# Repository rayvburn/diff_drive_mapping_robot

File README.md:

# diff_drive_mapping_robot
This is the ROS driver for the Raspberry Pi based differential drive robot that was built as a part of my MSc thesis. 

Base of the robot was made of acrylic glass. The locomotion is provided by 3 wheels, including 1 caster. The two-wheel differential drive based on DC motors makes the machine nonholonomic.

Within the electronic part of the robot's construction, a printed circuit board was designed. All the necessary electronical components including reflective sensors used to measure the distance from obstacles were placed on the board. The sensor providing the largest amount of data is the camera. It is integrated with the Raspberry Pi microcomputer. The extension of the microcomputer's tasks to the reading of wheel positions and motor control allowed to use its resources efficiently and to avoid adding an extra microcontroller.

Looking at the PCB project (made in KiCad) should give you some idea what components to use if you plan to make a copy of it.

The robot is intended to work together with remote machine like PC that performs some more sophisticated duties. It was created to interface with ORB-SLAM2 well.

# Installation instructions

The package contents should be placed and compiled both on PC and on RPi's SD card. It was tested only on ROS Kinetic (running on Ubuntu 16.04).

wiringPi library is needed (http://wiringpi.com/). A script to install it on Raspberry Pi was provided.

raspicam_node (https://github.com/UbiquityRobotics/raspicam_node) is required if you will use Raspberry Pi camera but isn't marked as dependency for the package. If you don't plan to use it, just remove appropriate line in robot/robot_offline .launch file (the one with inclusion of raspicam_node's .launch).

# Usage

If a Raspberry Pi is present within a local Wi-Fi network

    roslaunch diff_drive_mapping_robot robot.launch

or for testing purposes (no RPi)

    roslaunch diff_drive_mapping_robot robot_offline.launch
    
# Notes
I highly recommend acquiring an Ubuntu image adequate for Raspberry Pi (with ROS Kinetic already installed) from here: https://downloads.ubiquityrobotics.com/pi.html

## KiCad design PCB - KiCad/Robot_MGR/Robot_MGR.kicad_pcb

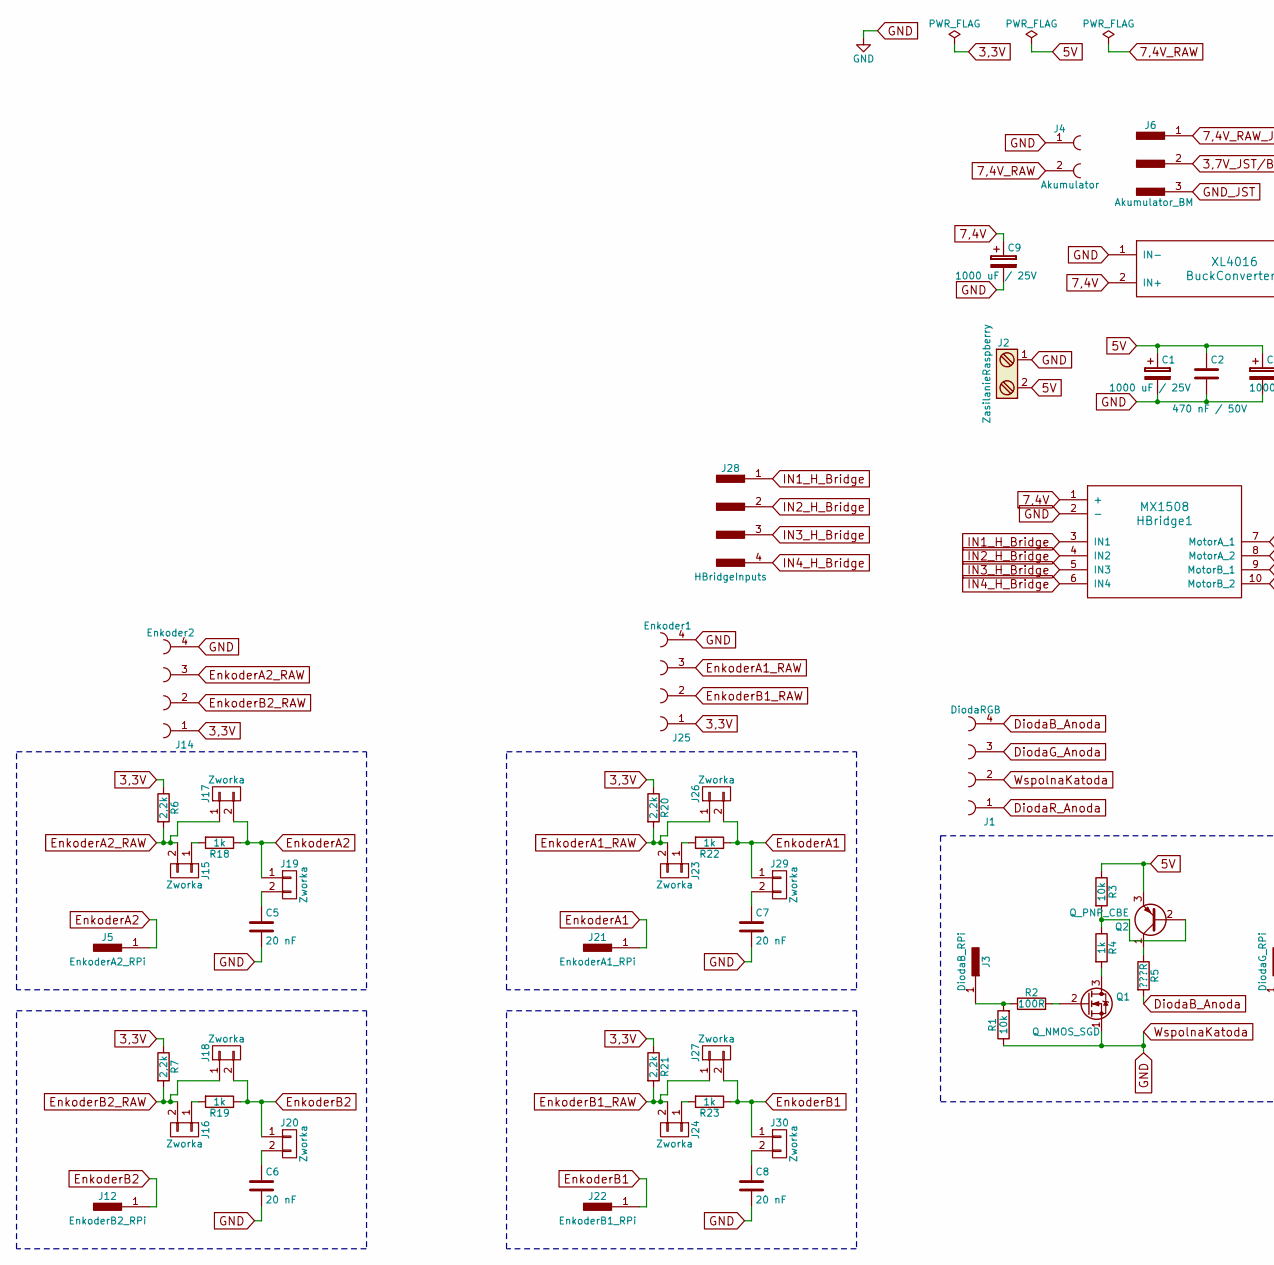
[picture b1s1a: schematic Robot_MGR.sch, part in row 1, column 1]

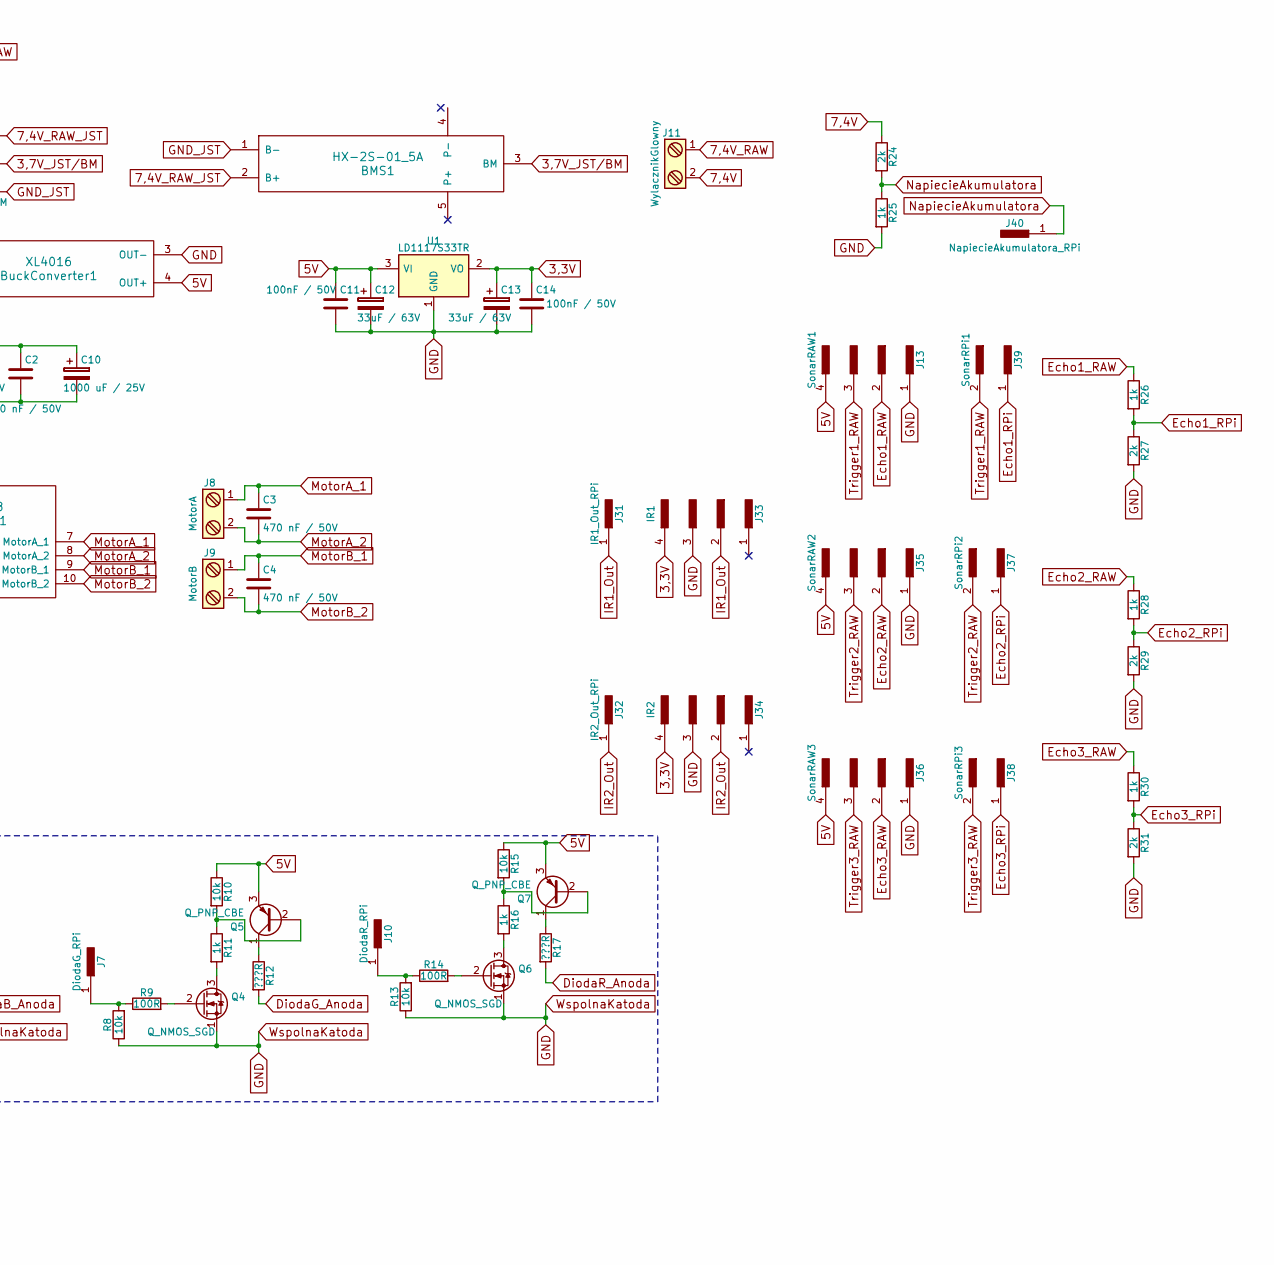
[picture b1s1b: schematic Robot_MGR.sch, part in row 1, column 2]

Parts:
BMS1: HX-2S-01_5A
BuckConverter1: XL4016
C1, C9, C10: 1000 uF / 25V; CP_Radial_D10.0mm_P5.00mm
C2, C3, C4: 470 nF / 50V; CP_Radial_Tantal_D5.0mm_P2.50mm
C5, C6, C7, C8: 20 nF; CP_Radial_Tantal_D5.0mm_P2.50mm
C11, C14: 100nF / 50V; C_Disc_D3.8mm_W2.6mm_P2.50mm
C12, C13: 33uF / 63V; CP_Radial_D6.3mm_P2.50mm
HBridge1: MX1508
J1: DiodaRGB; JST_EH_B04B-EH-A_04x2.50mm_Straight
J2: ZasilanieRaspberry; TerminalBlock_Philmore_TB132_02x5mm_Straight
J3: DiodaB_RPi; Pin_Header_Straight_1x01_Pitch2.54mm
J4: Akumulator; XT60
J5: EnkoderA2_RPi; Pin_Header_Straight_1x01_Pitch2.54mm
J6: Akumulator_BM; JST_XH_B03B-XH-A_03x2.50mm_Straight
J7: DiodaG_RPi; Pin_Header_Straight_1x01_Pitch2.54mm
J8: MotorA; TerminalBlock_Philmore_TB132_02x5mm_Straight
J9: MotorB; TerminalBlock_Philmore_TB132_02x5mm_Straight
J10: DiodaR_RPi; Pin_Header_Straight_1x01_Pitch2.54mm
J11: WylacznikGlowny; TerminalBlock_Philmore_TB132_02x5mm_Straight
J12: EnkoderB2_RPi; Pin_Header_Straight_1x01_Pitch2.54mm
J13: SonarRAW1; JST_XH_B04B-XH-A_04x2.50mm_Straight
J14: Enkoder2; JST_EH_B04B-EH-A_04x2.50mm_Straight
J15, J16, J17, J18, J19, J20, J23, J24, J26, J27, J29, J30: Zworka; Pin_Header_Straight_1x02_Pitch2.54mm
J21: EnkoderA1_RPi; Pin_Header_Straight_1x01_Pitch2.54mm
J22: EnkoderB1_RPi; Pin_Header_Straight_1x01_Pitch2.54mm
J25: Enkoder1; JST_EH_B04B-EH-A_04x2.50mm_Straight
J28: HBridgeInputs; Pin_Header_Straight_1x04_Pitch2.54mm
J31: IR1_Out_RPi; Pin_Header_Straight_1x01_Pitch2.54mm
J32: IR2_Out_RPi; Pin_Header_Straight_1x01_Pitch2.54mm
J33: IR1; Pin_Header_Straight_1x04_Pitch2.54mm
J34: IR2; Pin_Header_Straight_1x04_Pitch2.54mm
J35: SonarRAW2; JST_XH_B04B-XH-A_04x2.50mm_Straight
J36: SonarRAW3; JST_XH_B04B-XH-A_04x2.50mm_Straight
J37: SonarRPi2; Pin_Header_Straight_1x02_Pitch2.54mm
J38: SonarRPi3; Pin_Header_Straight_1x02_Pitch2.54mm
J39: SonarRPi1; Pin_Header_Straight_1x02_Pitch2.54mm
J40: NapiecieAkumulatora_RPi; Pin_Header_Straight_1x01_Pitch2.54mm
Q1, Q4, Q6: Q_NMOS_SGD; TO-92_Inline_Wide
Q2, Q5, Q7: Q_PNP_CBE; TO-92_Inline_Wide
R1, R3, R8, R10, R13, R15: 10k; R_Axial_DIN0207_L6.3mm_D2.5mm_P10.16mm_Horizontal
R2, R9, R14: 100R; R_Axial_DIN0207_L6.3mm_D2.5mm_P10.16mm_Horizontal
R4, R11, R16, R18, R19, R22, R23, R25, R26, R28, R30: 1k; R_Axial_DIN0207_L6.3mm_D2.5mm_P10.16mm_Horizontal
R5, R12, R17: ???R; R_Axial_DIN0207_L6.3mm_D2.5mm_P10.16mm_Horizontal
R6, R7, R20, R21: 2,2k; R_Axial_DIN0207_L6.3mm_D2.5mm_P10.16mm_Horizontal
R24, R27, R29, R31: 2k; R_Axial_DIN0207_L6.3mm_D2.5mm_P10.16mm_Horizontal
U1: LD1117S33TR; TO-220-3_Vertical

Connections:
3,3V: C13.1, C14.1, J14.1, J25.1, J33.4, J34.4, R6.1, R7.1, R20.1, R21.1, U1.2 (VO)
3,7V_JST/BM: BMS1.3 (BM), J6.2
5V: BuckConverter1.4 (OUT+), C1.1, C2.1, C10.1, C11.1, C12.1, J2.2, J13.4, J35.4, J36.4, Q2.3 (E), Q5.3 (E), Q7.3 (E), R3.1, R10.1, R15.1, U1.3 (VI)
7,4V: BuckConverter1.2 (IN+), C9.1, HBridge1.1 (+), J11.2, R24.1
7,4V_RAW: J4.2, J11.1
7,4V_RAW_JST: BMS1.2 (B+), J6.1
DiodaB_Anoda: J1.4, R5.2
DiodaG_Anoda: J1.3, R12.2
DiodaR_Anoda: J1.1, R17.2
Echo1_RAW: J13.2, R26.1
Echo1_RPi: J39.1, R26.2, R27.1
Echo2_RAW: J35.2, R28.1
Echo2_RPi: J37.1, R28.2, R29.1
Echo3_RAW: J36.2, R30.1
Echo3_RPi: J38.1, R30.2, R31.1
EnkoderA1: J21.1, J26.2, J29.1, R22.1
EnkoderA1_RAW: J23.2, J25.3, J26.1, R20.2
EnkoderA2: J5.1, J17.2, J19.1, R18.1
EnkoderA2_RAW: J14.3, J15.2, J17.1, R6.2
EnkoderB1: J22.1, J27.2, J30.1, R23.1
EnkoderB1_RAW: J24.2, J25.2, J27.1, R21.2
EnkoderB2: J12.1, J18.2, J20.1, R19.1
EnkoderB2_RAW: J14.2, J16.2, J18.1, R7.2
GND: BuckConverter1.1 (IN-), BuckConverter1.3 (OUT-), C1.2, C2.2, C5.2, C6.2, C7.2, C8.2, C9.2, C10.2, C11.2, C12.2, C13.2, C14.2, HBridge1.2 (-), J1.2, J2.1, J4.1, J13.1, J14.4, J25.4, J33.3, J34.3, J35.1, J36.1, Q1.1 (S), Q4.1 (S), Q6.1 (S), R1.1, R8.1, R13.1, R25.2, R27.2, R29.2, R31.2, U1.1 (GND)
GND_JST: BMS1.1 (B-), J6.3
IN1_H_Bridge: HBridge1.3 (IN1), J28.1
IN2_H_Bridge: HBridge1.4 (IN2), J28.2
IN3_H_Bridge: HBridge1.5 (IN3), J28.3
IN4_H_Bridge: HBridge1.6 (IN4), J28.4
IR1_Out: J31.1, J33.2
IR2_Out: J32.1, J34.2
MotorA_1: C3.1, HBridge1.7 (MotorA_1), J8.1
MotorA_2: C3.2, HBridge1.8 (MotorA_2), J8.2
MotorB_1: C4.1, HBridge1.9 (MotorB_1), J9.1
MotorB_2: C4.2, HBridge1.10 (MotorB_2), J9.2
NapiecieAkumulatora: J40.1, R24.2, R25.1
unnamed: C5.1, J19.2
unnamed: C6.1, J20.2
unnamed: C7.1, J29.2
unnamed: C8.1, J30.2
unnamed: J3.1, R1.2, R2.1
unnamed: J7.1, R8.2, R9.1
unnamed: J10.1, R13.2, R14.1
unnamed: J15.1, R18.2
unnamed: J16.1, R19.2
unnamed: J23.1, R22.2
unnamed: J24.1, R23.2
unnamed: Q1.2 (G), R2.2
unnamed: Q1.3 (D), R4.2
unnamed: Q2.1 (C), R5.1
unnamed: Q2.2 (B), R3.2, R4.1
unnamed: Q4.2 (G), R9.2
unnamed: Q4.3 (D), R11.2
unnamed: Q5.1 (C), R12.1
unnamed: Q5.2 (B), R10.2, R11.1
unnamed: Q6.2 (G), R14.2
unnamed: Q6.3 (D), R16.2
unnamed: Q7.1 (C), R17.1
unnamed: Q7.2 (B), R15.2, R16.1
Trigger1_RAW: J13.3, J39.2
Trigger2_RAW: J35.3, J37.2
Trigger3_RAW: J36.3, J38.2

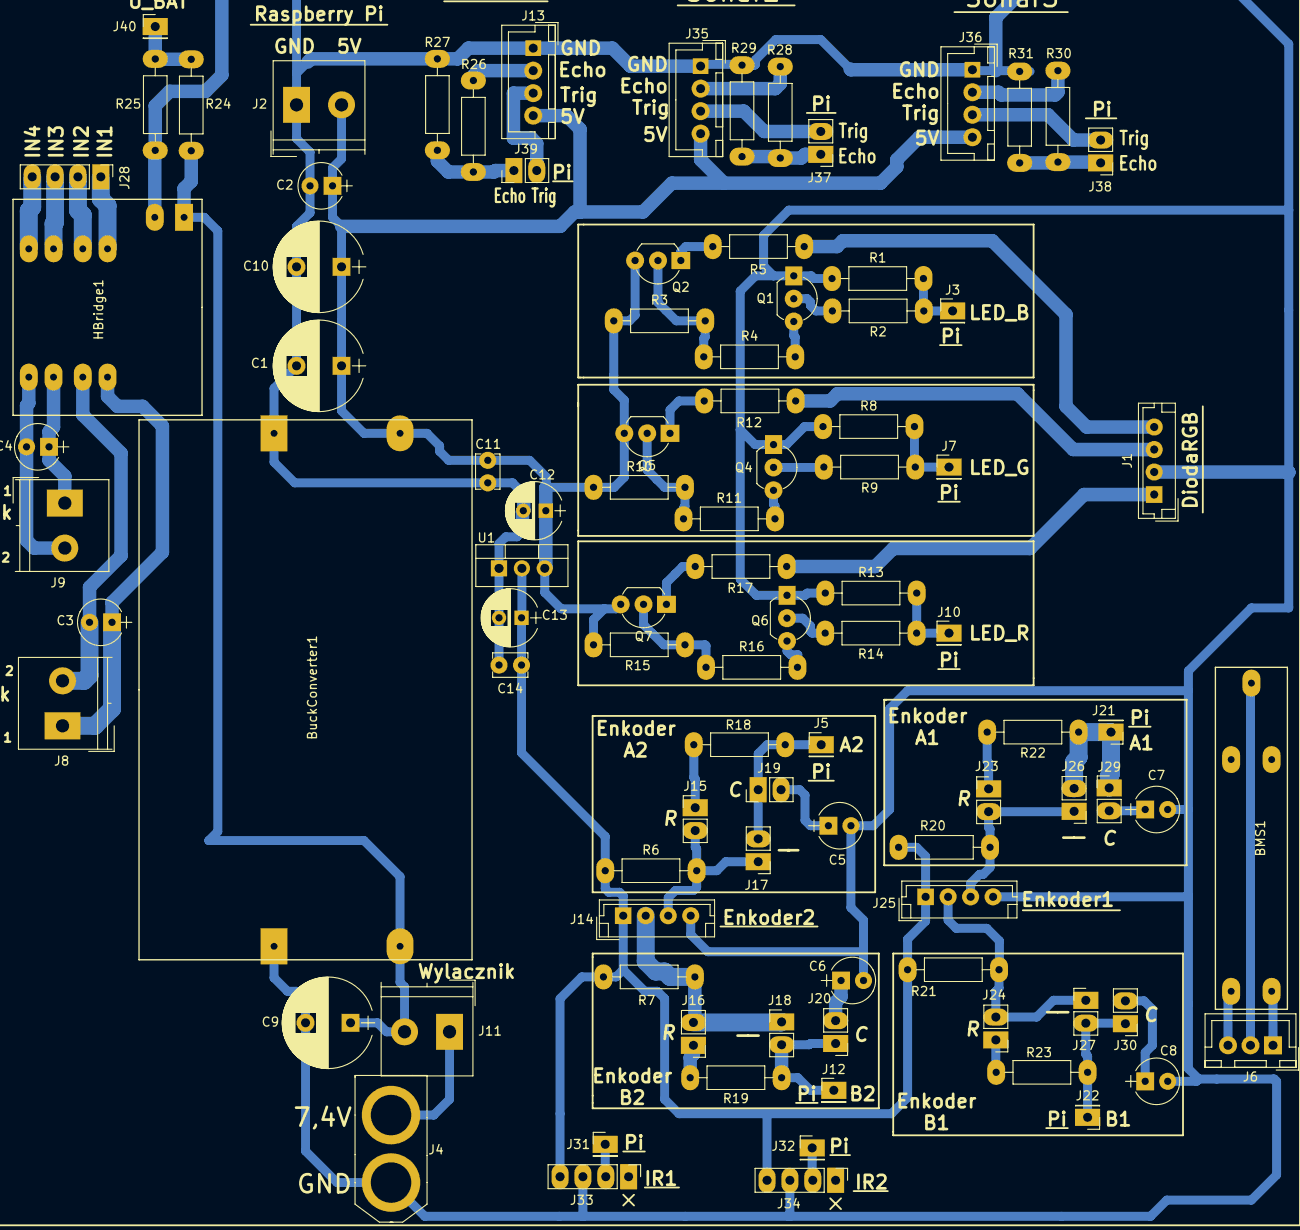
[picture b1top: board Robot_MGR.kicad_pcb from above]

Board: 2 copper layers, 95 parts (0 on the bottom side), 62 nets.

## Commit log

2018-08-15 Add files via upload
    v0.9.0 - TODO: reading battery voltage by an external ADC
2018-08-15 just a short description of the contents
2018-08-15 Add files via upload
    schematic and PCB design
2018-08-15 script that should be placed in RPi's ~/catkin_ws
2018-08-15 script from PC (placed in /opt/ros/kinetic/)
2018-08-15 mobile base photos
